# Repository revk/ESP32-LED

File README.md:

# ESP32-LED

Now at [Codeberg](https://codeberg.org/RevK/ESP32-LED)

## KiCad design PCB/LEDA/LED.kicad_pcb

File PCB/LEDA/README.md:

# LEDA

## Trademark

This is an open source project, but bear in mind you cannot sell boards or cases bearing the Andrews & Arnold Ltd name, the A&A logo, the registered trademark AJK logo, or the GS1 allocated EANs assigned to Andrews & Arnold Ltd.

## PCB Designs

These files are for use with [KiCAD](https://www.kicad.org).

- [LED](LED.kicad_pro)

## 3D

3D case designs are normally automatically created from the PCB so as to ensure correct details and placement of apertures, etc.

|Design|Bottom|Top|Combined|
|------|------|---|--------|
|LED||||

## PCB Images

---

*Auto generated README.md 2025-11-15T10:07:33*

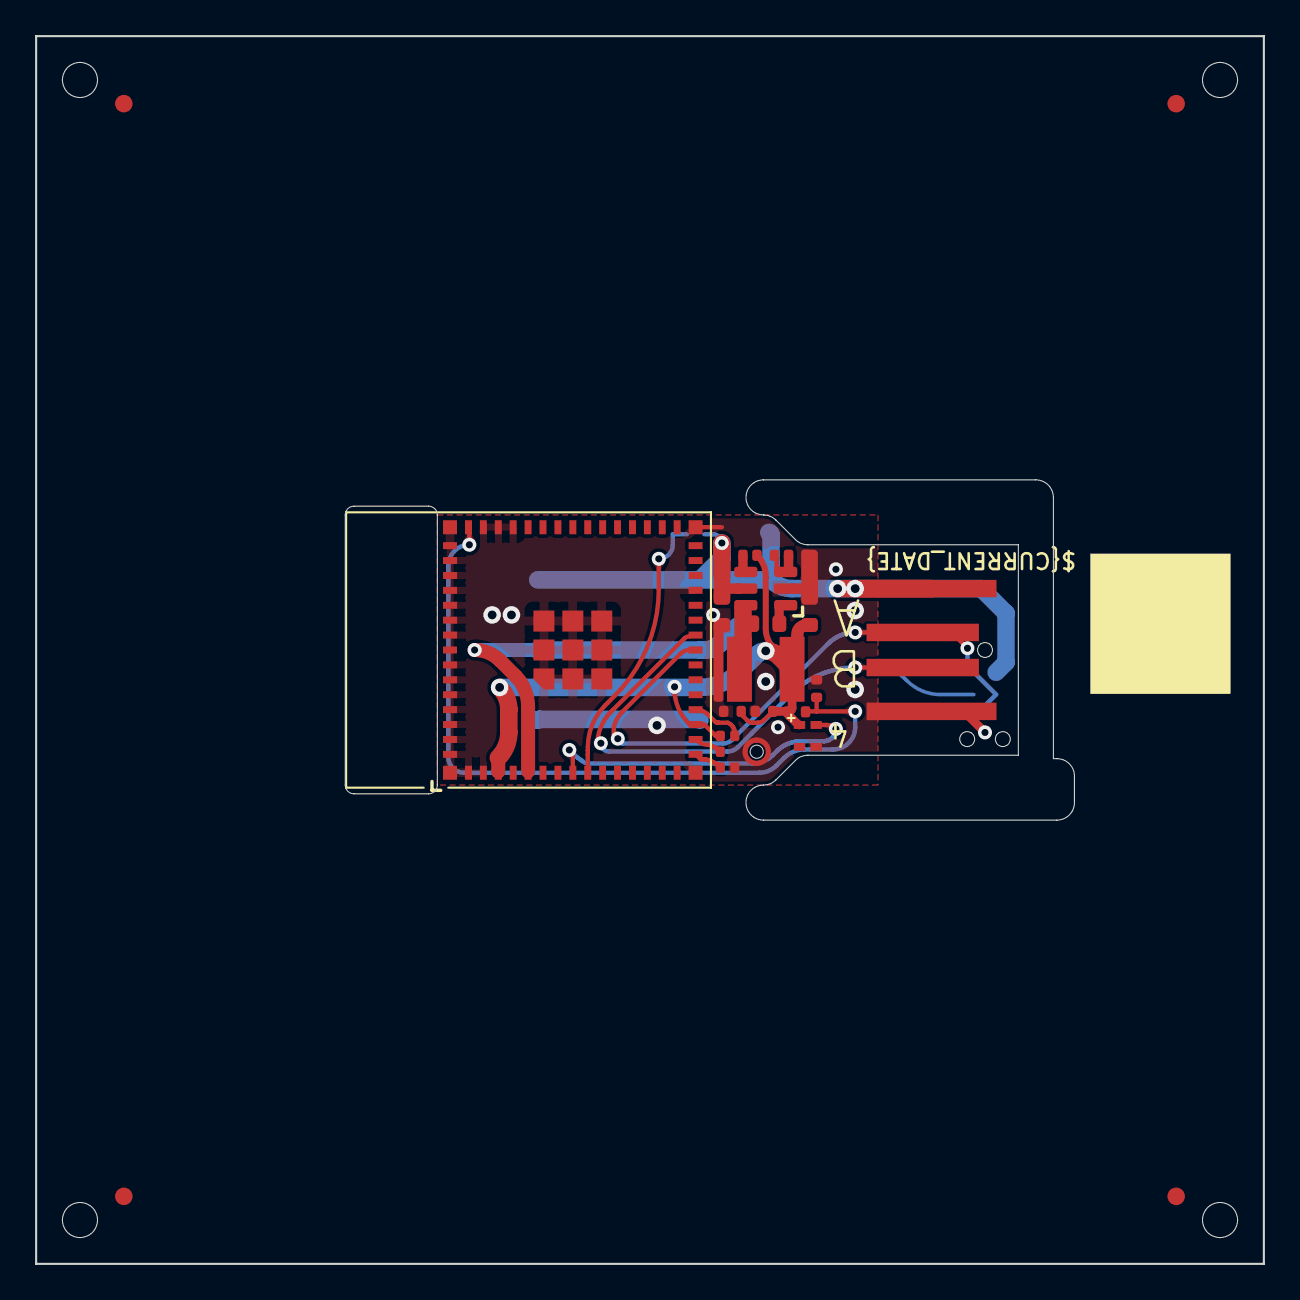
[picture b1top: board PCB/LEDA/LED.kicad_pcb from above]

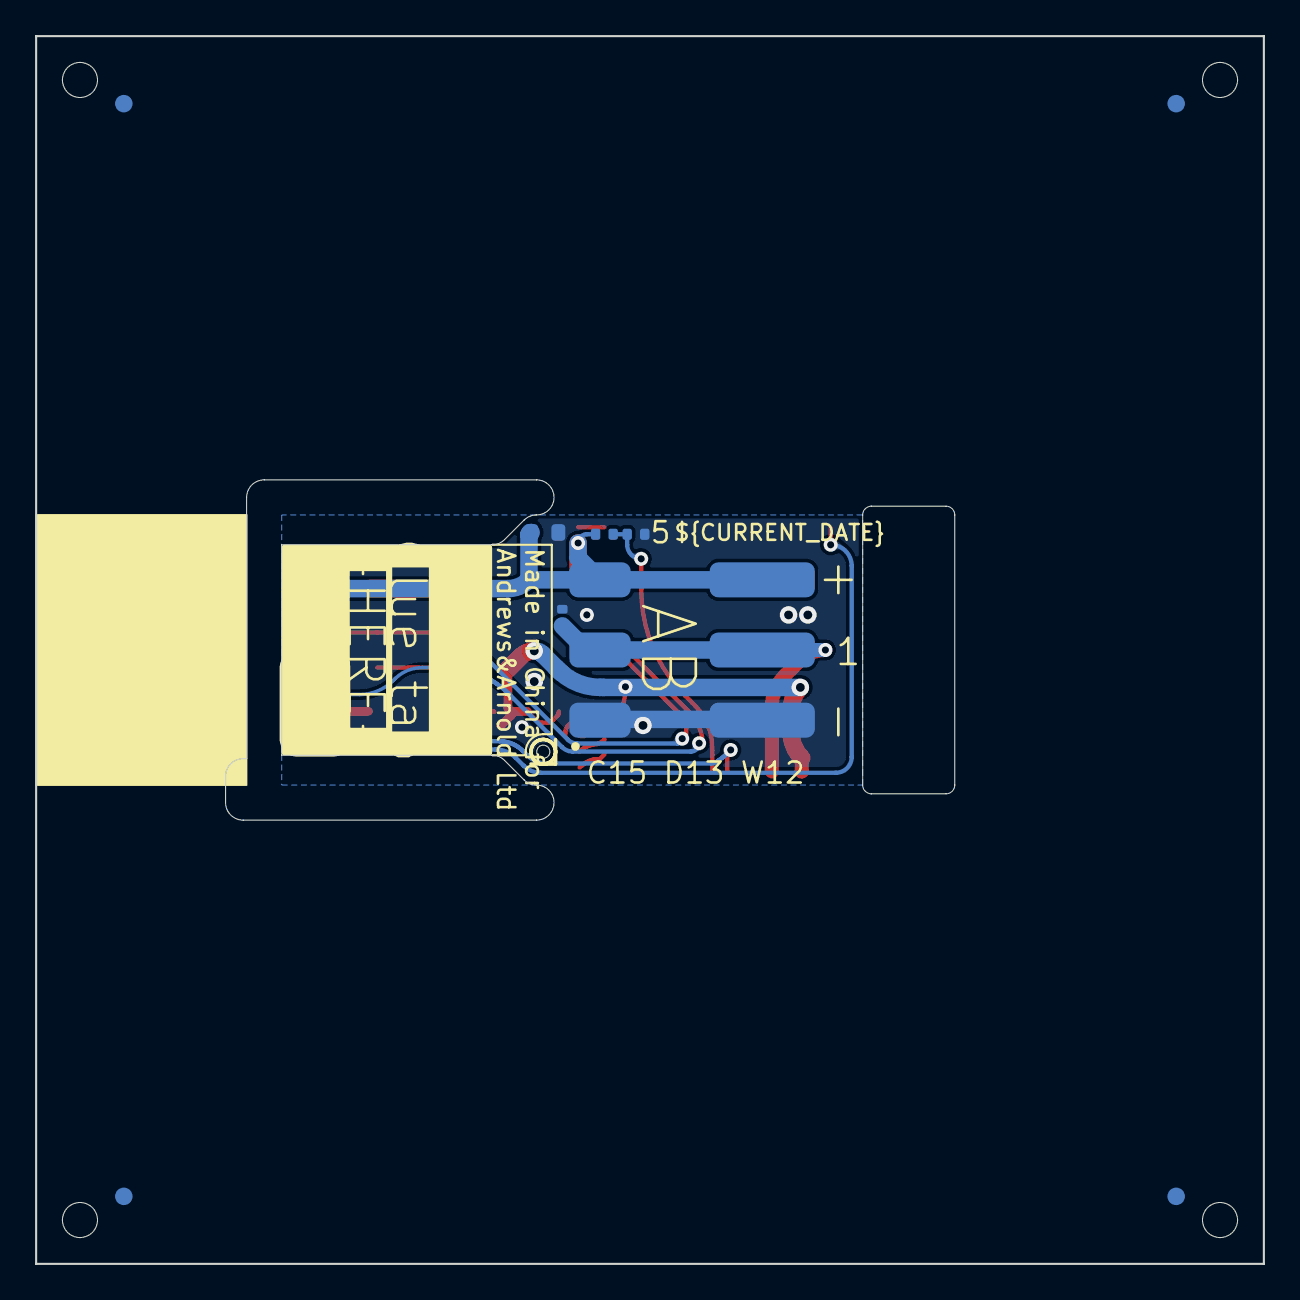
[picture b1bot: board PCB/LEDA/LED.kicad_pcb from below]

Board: 2 copper layers, 70.0 x 70.0 mm, 25 parts (8 on the bottom side), 12 nets.

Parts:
C1: 100nF; C_0402
C2: 22uF; C_0402
C3: 1uF; C_0402
C4: 10uF 35V; C_0603
C6: 10uF 35V; C_0603_
C7: 10uF 6.3V; C_0603_
C8: 100nF; C_0603_
D1: XL-1010RGBC-WS2812B; SMD1615
D2: DFN1006-2L
J1: USB_A; USB-A-PCB
J2: Conn_01x03; WAGO-2060-453-998-404-O
J3: TC2030-USB-NL-DS; Tag-Connect_TC2030-IDC-NL_2x03_P1.27mm_Vertical
L2: 10uH; L_4x4_
PCB1: 70x70; PCB7070
R1, R3: 10K; R_0402
R2: 124K; R_0402
R9: 124k; R_0402_
R10: 39k2; R_0402_
R11: 1M; R_0402_
U1: ICS43434_MEMS_Mic
U2: ESP32-S3-MINI-1
U5: MD8942; SOT-23-6-MD8942
V1, V2: 70; VCUT70N

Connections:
+3.3V: C1.1, C2.1, D1.3 (+), R1.1, U1.5 (VDD), U2.3 (3V3), U2.18 (GPIO14), U5.8 (VOUT)
ADC: R2.2, R3.1, U2.9 (GPIO5)
D+: J1.3 (D+), J3.4 (D+), U2.24 (GPIO20)
D-: J1.2 (D-), J3.2 (NC), J3.3 (D-), J3.6 (NC), U2.23 (GPIO19)
DC: C4.1, J1.1 (VBUS), J2.3, J3.1 (VBUS), R2.1, U5.5 (VIN)
GND: C1.2, C2.2, C3.2, C4.2, D1.1 (-), D2.1, J1.4 (GND), J2.1, J3.5 (GND), R3.2, U1.2 (LR), U1.3 (GND), U2.1 (GND), U2.2 (GND), U2.27 (GPIO47), U2.42 (GND), U2.43 (GND), U2.44 (GPIO46), U2.46 (GND), U2.47 (GND), U2.48 (GND), U2.49 (GND), U2.50 (GND), U2.51 (GND), U2.52 (GND), U2.53 (GND), U2.54 (GND), U2.55 (GND), U2.56 (GND), U2.57 (GND), U2.58 (GND), U2.59 (GND), U2.60 (GND), U2.61 (GND), U2.62 (GND), U2.63 (GND), U2.64 (GND), U2.65 (GND), U5.2 (GND), U5.7 (GND)
LED1: D1.2 (I), U2.8 (GPIO4)
LED2: D2.2, J2.2, U2.5 (GPIO1)
unnamed: C3.1, R1.2, U2.45 (EN)
SCK: U1.4 (SCK), U2.19 (GPIO15)
SD: U1.6 (SD), U2.17 (GPIO13)
WS: U1.1 (WS), U2.16 (GPIO12)

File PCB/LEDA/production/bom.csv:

Designator,Footprint,Quantity,Value,LCSC Part #
C1,C_0402,1,100nF,
C2,C_0402,1,22uF,
C3,C_0402,1,1uF,
C4,C_0603,1,10uF 35V,C194427
C6,C_0603_,1,10uF 35V,C194427
C7,C_0603_,1,10uF 6.3V,C1691
C8,C_0603_,1,100nF,
D1,SMD1615,1,XL-1010RGBC-WS2812B,C5349954
D2,DFN1006-2L,1,~,C5137770
J2,WAGO-2060-453-998-404,1,Conn_01x03,C2765056
L2,L_4x4_,1,10uH,
"R1, R3",R_0402,2,10K,
R10,R_0402_,1,39k2,
R11,R_0402_,1,1M,
R2,R_0402,1,124K,
R9,R_0402_,1,124k,
U1,ICS43434_MEMS_Mic,1,ICS43434_MEMS_Mic,C5656610
U2,ESP32-S3-MINI-1,1,ESP32-S3-MINI-1,C3013941
U5,SOT-23-6-MD8942,1,MD8942,C2684786

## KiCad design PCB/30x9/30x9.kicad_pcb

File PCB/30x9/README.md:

# 30x9

## Trademark

This is an open source project, but bear in mind you cannot sell boards or cases bearing the Andrews & Arnold Ltd name, the A&A logo, the registered trademark AJK logo, or the GS1 allocated EANs assigned to Andrews & Arnold Ltd.

## PCB Designs

These files are for use with [KiCAD](https://www.kicad.org).

- [30x9](30x9.kicad_pro)

## PCB Images

---

*Auto generated README.md 2025-11-09T11:15:14*

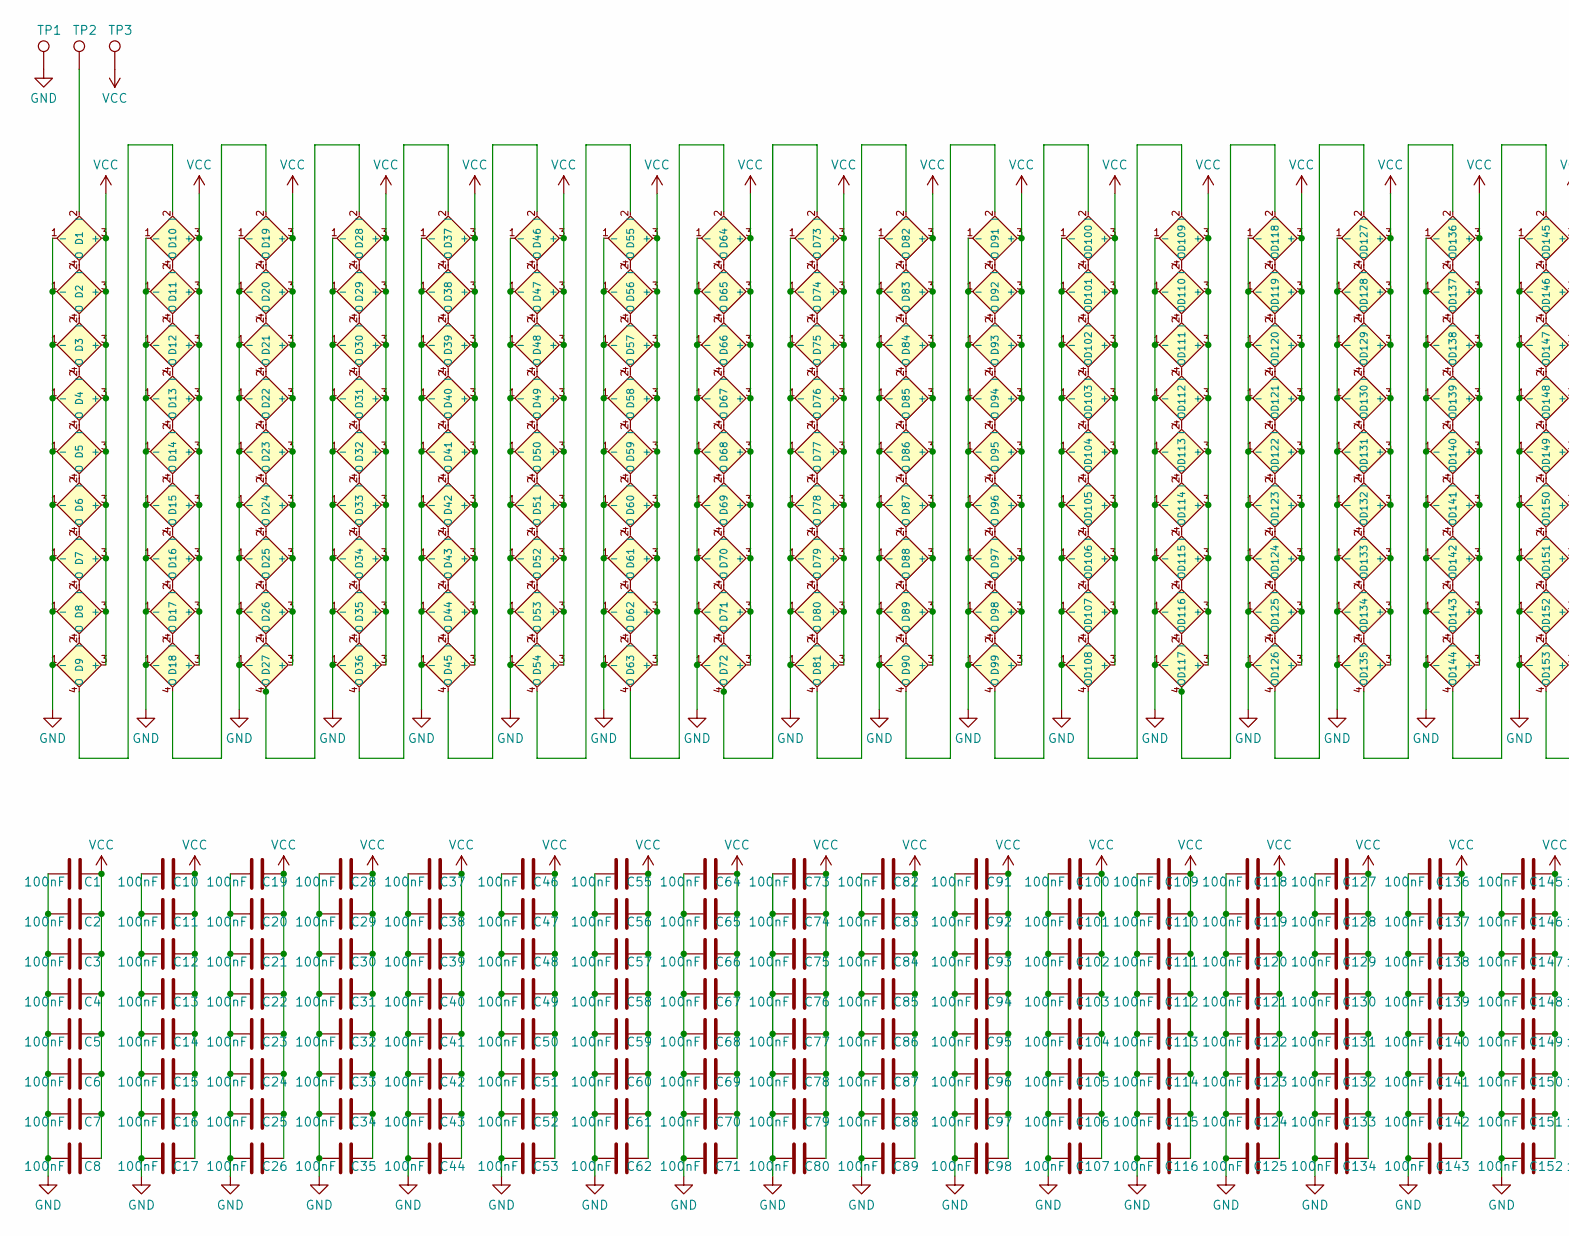
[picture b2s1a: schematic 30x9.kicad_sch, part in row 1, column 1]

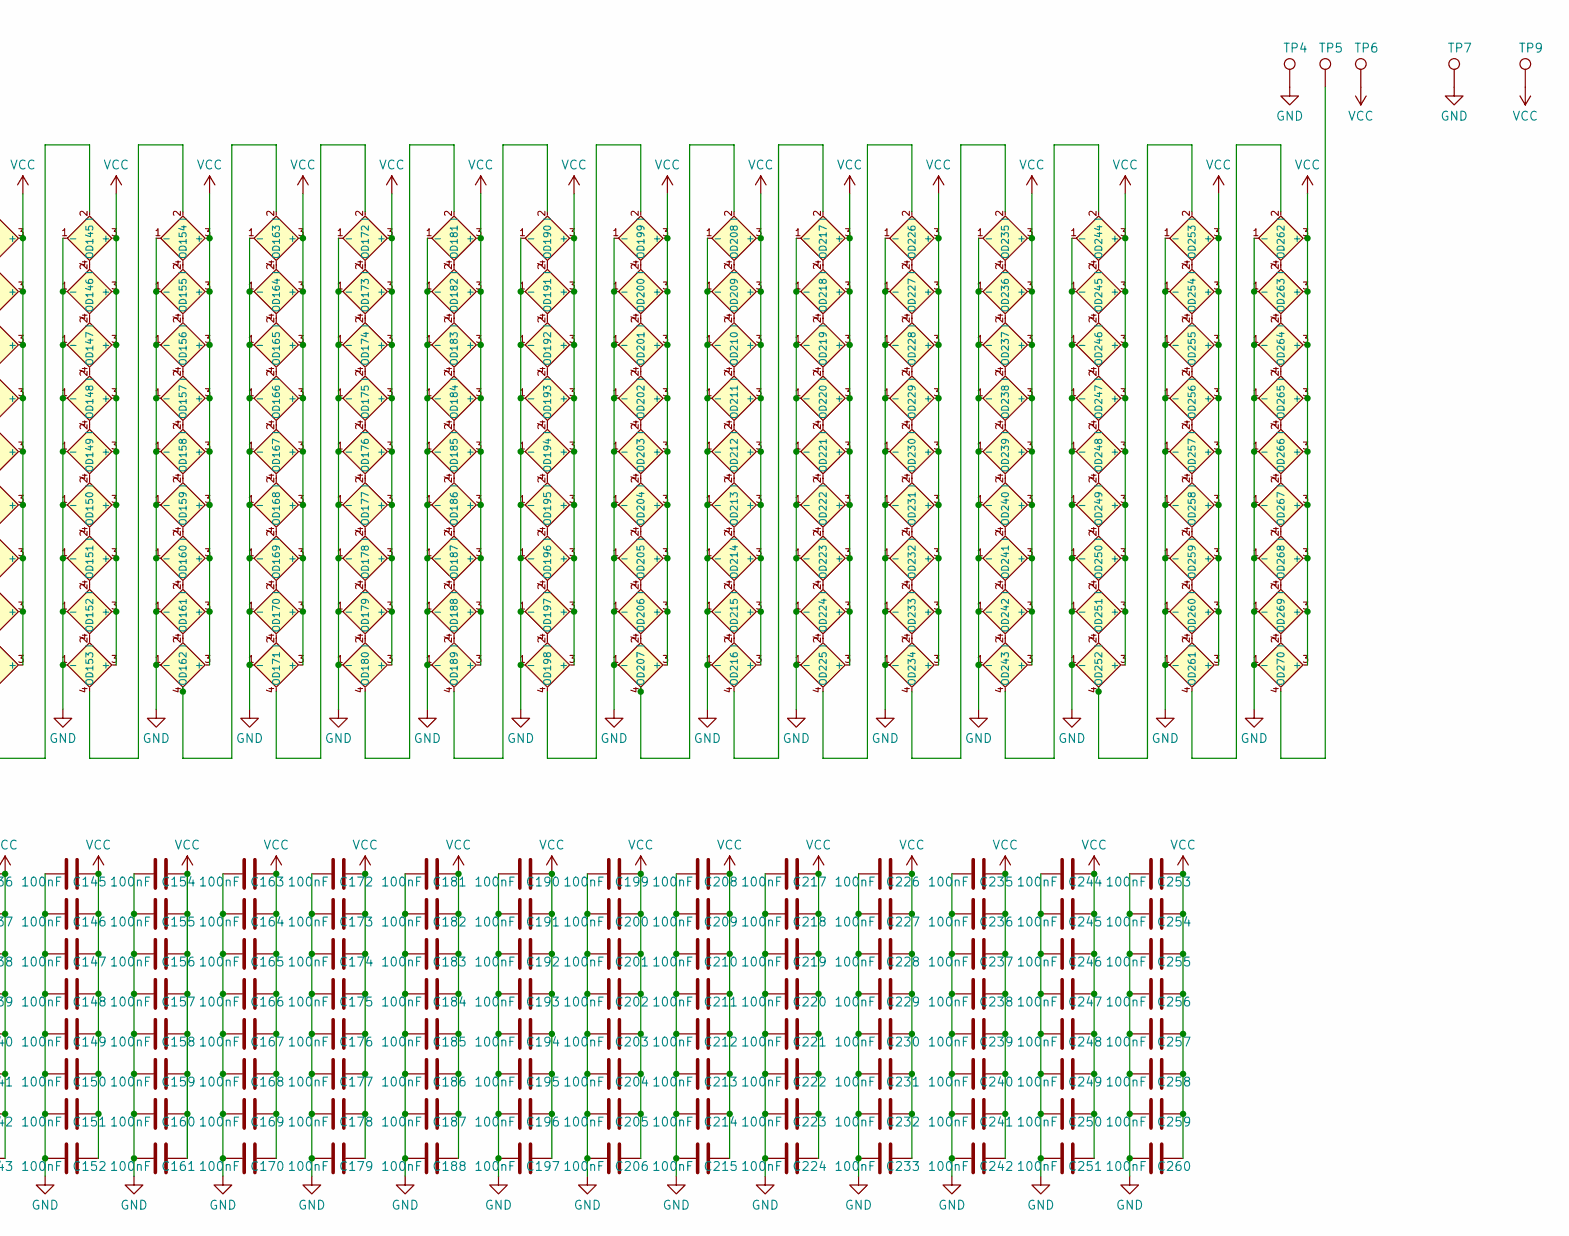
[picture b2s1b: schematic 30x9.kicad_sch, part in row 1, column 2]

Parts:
C1, C2, C3, C4, C5, C6, C7, C8, C10, C11, C12, C13, C14, C15, C16, C17, C19, C20, C21, C22, C23, C24, C25, C26, C28, C29, C30, C31, C32, C33, C34, C35, C37, C38, C39, C40, C41, C42, C43, C44, C46, C47, C48, C49, C50, C51, C52, C53, C55, C56, C57, C58, C59, C60, C61, C62, C64, C65, C66, C67, C68, C69, C70, C71, C73, C74, C75, C76, C77, C78, C79, C80, C82, C83, C84, C85, C86, C87, C88, C89, C91, C92, C93, C94, C95, C96, C97, C98, C100, C101, C102, C103, C104, C105, C106, C107, C109, C110, C111, C112, C113, C114, C115, C116, C118, C119, C120, C121, C122, C123, C124, C125, C127, C128, C129, C130, C131, C132, C133, C134, C136, C137, C138, C139, C140, C141, C142, C143, C145, C146, C147, C148, C149, C150, C151, C152, C154, C155, C156, C157, C158, C159, C160, C161, C163, C164, C165, C166, C167, C168, C169, C170, C172, C173, C174, C175, C176, C177, C178, C179, C181, C182, C183, C184, C185, C186, C187, C188, C190, C191, C192, C193, C194, C195, C196, C197, C199, C200, C201, C202, C203, C204, C205, C206, C208, C209, C210, C211, C212, C213, C214, C215, C217, C218, C219, C220, C221, C222, C223, C224, C226, C227, C228, C229, C230, C231, C232, C233, C235, C236, C237, C238, C239, C240, C241, C242, C244, C245, C246, C247, C248, C249, C250, C251, C253, C254, C255, C256, C257, C258, C259, C260: 100nF; C_0201; MPN C76934
D1, D2, D3, D4, D5, D6, D7, D8, D9, D10, D11, D12, D13, D14, D15, D16, D17, D18, D19, D20, D21, D22, D23, D24, D25, D26, D27, D28, D29, D30, D31, D32, D33, D34, D35, D36, D37, D38, D39, D40, D41, D42, D43, D44, D45, D46, D47, D48, D49, D50, D51, D52, D53, D54, D55, D56, D57, D58, D59, D60, D61, D62, D63, D64, D65, D66, D67, D68, D69, D70, D71, D72, D73, D74, D75, D76, D77, D78, D79, D80, D81, D82, D83, D84, D85, D86, D87, D88, D89, D90, D91, D92, D93, D94, D95, D96, D97, D98, D99, D100, D101, D102, D103, D104, D105, D106, D107, D108, D109, D110, D111, D112, D113, D114, D115, D116, D117, D118, D119, D120, D121, D122, D123, D124, D125, D126, D127, D128, D129, D130, D131, D132, D133, D134, D135, D136, D137, D138, D139, D140, D141, D142, D143, D144, D145, D146, D147, D148, D149, D150, D151, D152, D153, D154, D155, D156, D157, D158, D159, D160, D161, D162, D163, D164, D165, D166, D167, D168, D169, D170, D171, D172, D173, D174, D175, D176, D177, D178, D179, D180, D181, D182, D183, D184, D185, D186, D187, D188, D189, D190, D191, D192, D193, D194, D195, D196, D197, D198, D199, D200, D201, D202, D203, D204, D205, D206, D207, D208, D209, D210, D211, D212, D213, D214, D215, D216, D217, D218, D219, D220, D221, D222, D223, D224, D225, D226, D227, D228, D229, D230, D231, D232, D233, D234, D235, D236, D237, D238, D239, D240, D241, D242, D243, D244, D245, D246, D247, D248, D249, D250, D251, D252, D253, D254, D255, D256, D257, D258, D259, D260, D261, D262, D263, D264, D265, D266, D267, D268, D269, D270: XL-1010RGBC-WS2812B; SMD1615; MPN C5349954
TP1, TP2, TP3, TP4, TP5, TP6, TP7, TP9: TestPoint; PAD-2mm

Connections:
GND: C1.1, C2.1, C3.1, C4.1, C5.1, C6.1, C7.1, C8.1, C10.1, C11.1, C12.1, C13.1, C14.1, C15.1, C16.1, C17.1, C19.1, C20.1, C21.1, C22.1, C23.1, C24.1, C25.1, C26.1, C28.1, C29.1, C30.1, C31.1, C32.1, C33.1, C34.1, C35.1, C37.1, C38.1, C39.1, C40.1, C41.1, C42.1, C43.1, C44.1, C46.1, C47.1, C48.1, C49.1, C50.1, C51.1, C52.1, C53.1, C55.1, C56.1, C57.1, C58.1, C59.1, C60.1, C61.1, C62.1, C64.1, C65.1, C66.1, C67.1, C68.1, C69.1, C70.1, C71.1, C73.1, C74.1, C75.1, C76.1, C77.1, C78.1, C79.1, C80.1, C82.1, C83.1, C84.1, C85.1, C86.1, C87.1, C88.1, C89.1, C91.1, C92.1, C93.1, C94.1, C95.1, C96.1, C97.1, C98.1, C100.1, C101.1, C102.1, C103.1, C104.1, C105.1, C106.1, C107.1, C109.1, C110.1, C111.1, C112.1, C113.1, C114.1, C115.1, C116.1, C118.1, C119.1, C120.1, C121.1, C122.1, C123.1, C124.1, C125.1, C127.1, C128.1, C129.1, C130.1, C131.1, C132.1, C133.1, C134.1, C136.1, C137.1, C138.1, C139.1, C140.1, C141.1, C142.1, C143.1, C145.1, C146.1, C147.1, C148.1, C149.1, C150.1, C151.1, C152.1, C154.1, C155.1, C156.1, C157.1, C158.1, C159.1, C160.1, C161.1, C163.1, C164.1, C165.1, C166.1, C167.1, C168.1, C169.1, C170.1, C172.1, C173.1, C174.1, C175.1, C176.1, C177.1, C178.1, C179.1, C181.1, C182.1, C183.1, C184.1, C185.1, C186.1, C187.1, C188.1, C190.1, C191.1, C192.1, C193.1, C194.1, C195.1, C196.1, C197.1, C199.1, C200.1, C201.1, C202.1, C203.1, C204.1, C205.1, C206.1, C208.1, C209.1, C210.1, C211.1, C212.1, C213.1, C214.1, C215.1, C217.1, C218.1, C219.1, C220.1, C221.1, C222.1, C223.1, C224.1, C226.1, C227.1, C228.1, C229.1, C230.1, C231.1, C232.1, C233.1, C235.1, C236.1, C237.1, C238.1, C239.1, C240.1, C241.1, C242.1, C244.1, C245.1, C246.1, C247.1, C248.1, C249.1, C250.1, C251.1, C253.1, C254.1, C255.1, C256.1, C257.1, C258.1, C259.1, C260.1, D1.1 (-), D2.1 (-), D3.1 (-), D4.1 (-), D5.1 (-), D6.1 (-), D7.1 (-), D8.1 (-), D9.1 (-), D10.1 (-), D11.1 (-), D12.1 (-), D13.1 (-), D14.1 (-), D15.1 (-), D16.1 (-), D17.1 (-), D18.1 (-), D19.1 (-), D20.1 (-), D21.1 (-), D22.1 (-), D23.1 (-), D24.1 (-), D25.1 (-), D26.1 (-), D27.1 (-), D28.1 (-), D29.1 (-), D30.1 (-), D31.1 (-), D32.1 (-), D33.1 (-), D34.1 (-), D35.1 (-), D36.1 (-), D37.1 (-), D38.1 (-), D39.1 (-), D40.1 (-), D41.1 (-), D42.1 (-), D43.1 (-), D44.1 (-), D45.1 (-), D46.1 (-), D47.1 (-), D48.1 (-), D49.1 (-), D50.1 (-), D51.1 (-), D52.1 (-), D53.1 (-), D54.1 (-), D55.1 (-), D56.1 (-), D57.1 (-), D58.1 (-), D59.1 (-), D60.1 (-), D61.1 (-), D62.1 (-), D63.1 (-), D64.1 (-), D65.1 (-), D66.1 (-), D67.1 (-), D68.1 (-), D69.1 (-), D70.1 (-), D71.1 (-), D72.1 (-), D73.1 (-), D74.1 (-), D75.1 (-), D76.1 (-), D77.1 (-), D78.1 (-), D79.1 (-), D80.1 (-), D81.1 (-), D82.1 (-), D83.1 (-), D84.1 (-), D85.1 (-), D86.1 (-), D87.1 (-), D88.1 (-), D89.1 (-), D90.1 (-), D91.1 (-), D92.1 (-), D93.1 (-), D94.1 (-), D95.1 (-), D96.1 (-), D97.1 (-), D98.1 (-), D99.1 (-), D100.1 (-), D101.1 (-), D102.1 (-), D103.1 (-), D104.1 (-), D105.1 (-), D106.1 (-), D107.1 (-), D108.1 (-), D109.1 (-), D110.1 (-), D111.1 (-), D112.1 (-), D113.1 (-), D114.1 (-), D115.1 (-), D116.1 (-), D117.1 (-), D118.1 (-), D119.1 (-), D120.1 (-), D121.1 (-), D122.1 (-), D123.1 (-), D124.1 (-), D125.1 (-), D126.1 (-), D127.1 (-), D128.1 (-), D129.1 (-), D130.1 (-), D131.1 (-), D132.1 (-), D133.1 (-), D134.1 (-), D135.1 (-), D136.1 (-), D137.1 (-), D138.1 (-), D139.1 (-), D140.1 (-), D141.1 (-), D142.1 (-), D143.1 (-), D144.1 (-), D145.1 (-), D146.1 (-), D147.1 (-), D148.1 (-), D149.1 (-), D150.1 (-), D151.1 (-), D152.1 (-), D153.1 (-), D154.1 (-), D155.1 (-), D156.1 (-), D157.1 (-), D158.1 (-), D159.1 (-), D160.1 (-), D161.1 (-), D162.1 (-), D163.1 (-), D164.1 (-), D165.1 (-), D166.1 (-), D167.1 (-), D168.1 (-), D169.1 (-), D170.1 (-), D171.1 (-), D172.1 (-), D173.1 (-), D174.1 (-), D175.1 (-), D176.1 (-), D177.1 (-), D178.1 (-), D179.1 (-), D180.1 (-), D181.1 (-), D182.1 (-), D183.1 (-), D184.1 (-), D185.1 (-), D186.1 (-), D187.1 (-), D188.1 (-), D189.1 (-), D190.1 (-), D191.1 (-), D192.1 (-), D193.1 (-), D194.1 (-), D195.1 (-), D196.1 (-), D197.1 (-), D198.1 (-), D199.1 (-), D200.1 (-), D201.1 (-), D202.1 (-), D203.1 (-), D204.1 (-), D205.1 (-), D206.1 (-), D207.1 (-), D208.1 (-), D209.1 (-), D210.1 (-), D211.1 (-), D212.1 (-), D213.1 (-), D214.1 (-), D215.1 (-), D216.1 (-), D217.1 (-), D218.1 (-), D219.1 (-), D220.1 (-), D221.1 (-), D222.1 (-), D223.1 (-), D224.1 (-), D225.1 (-), D226.1 (-), D227.1 (-), D228.1 (-), D229.1 (-), D230.1 (-), D231.1 (-), D232.1 (-), D233.1 (-), D234.1 (-), D235.1 (-), D236.1 (-), D237.1 (-), D238.1 (-), D239.1 (-), D240.1 (-), D241.1 (-), D242.1 (-), D243.1 (-), D244.1 (-), D245.1 (-), D246.1 (-), D247.1 (-), D248.1 (-), D249.1 (-), D250.1 (-), D251.1 (-), D252.1 (-), D253.1 (-), D254.1 (-), D255.1 (-), D256.1 (-), D257.1 (-), D258.1 (-), D259.1 (-), D260.1 (-), D261.1 (-), D262.1 (-), D263.1 (-), D264.1 (-), D265.1 (-), D266.1 (-), D267.1 (-), D268.1 (-), D269.1 (-), D270.1 (-), TP1.1, TP4.1, TP7.1
unnamed: D1.2 (I), TP2.1
unnamed: D1.4 (O), D2.2 (I)
unnamed: D2.4 (O), D3.2 (I)
unnamed: D3.4 (O), D4.2 (I)
unnamed: D4.4 (O), D5.2 (I)
unnamed: D5.4 (O), D6.2 (I)
unnamed: D6.4 (O), D7.2 (I)
unnamed: D7.4 (O), D8.2 (I)
unnamed: D8.4 (O), D9.2 (I)
unnamed: D9.4 (O), D10.2 (I)
unnamed: D10.4 (O), D11.2 (I)
unnamed: D11.4 (O), D12.2 (I)
unnamed: D12.4 (O), D13.2 (I)
unnamed: D13.4 (O), D14.2 (I)
unnamed: D14.4 (O), D15.2 (I)
unnamed: D15.4 (O), D16.2 (I)
unnamed: D16.4 (O), D17.2 (I)
unnamed: D17.4 (O), D18.2 (I)
unnamed: D18.4 (O), D19.2 (I)
unnamed: D19.4 (O), D20.2 (I)
unnamed: D20.4 (O), D21.2 (I)
unnamed: D21.4 (O), D22.2 (I)
unnamed: D22.4 (O), D23.2 (I)
unnamed: D23.4 (O), D24.2 (I)
unnamed: D24.4 (O), D25.2 (I)
unnamed: D25.4 (O), D26.2 (I)
unnamed: D26.4 (O), D27.2 (I)
unnamed: D27.4 (O), D28.2 (I)
unnamed: D28.4 (O), D29.2 (I)
unnamed: D29.4 (O), D30.2 (I)
unnamed: D30.4 (O), D31.2 (I)
unnamed: D31.4 (O), D32.2 (I)
unnamed: D32.4 (O), D33.2 (I)
unnamed: D33.4 (O), D34.2 (I)
unnamed: D34.4 (O), D35.2 (I)
unnamed: D35.4 (O), D36.2 (I)
unnamed: D36.4 (O), D37.2 (I)
unnamed: D37.4 (O), D38.2 (I)
unnamed: D38.4 (O), D39.2 (I)
unnamed: D39.4 (O), D40.2 (I)
unnamed: D40.4 (O), D41.2 (I)
unnamed: D41.4 (O), D42.2 (I)
unnamed: D42.4 (O), D43.2 (I)
unnamed: D43.4 (O), D44.2 (I)
unnamed: D44.4 (O), D45.2 (I)
unnamed: D45.4 (O), D46.2 (I)
unnamed: D46.4 (O), D47.2 (I)
unnamed: D47.4 (O), D48.2 (I)
unnamed: D48.4 (O), D49.2 (I)
unnamed: D49.4 (O), D50.2 (I)
unnamed: D50.4 (O), D51.2 (I)
unnamed: D51.4 (O), D52.2 (I)
unnamed: D52.4 (O), D53.2 (I)
unnamed: D53.4 (O), D54.2 (I)
unnamed: D54.4 (O), D55.2 (I)
unnamed: D55.4 (O), D56.2 (I)
unnamed: D56.4 (O), D57.2 (I)
unnamed: D57.4 (O), D58.2 (I)
unnamed: D58.4 (O), D59.2 (I)
unnamed: D59.4 (O), D60.2 (I)
unnamed: D60.4 (O), D61.2 (I)
unnamed: D61.4 (O), D62.2 (I)
unnamed: D62.4 (O), D63.2 (I)
unnamed: D63.4 (O), D64.2 (I)
unnamed: D64.4 (O), D65.2 (I)
unnamed: D65.4 (O), D66.2 (I)
unnamed: D66.4 (O), D67.2 (I)
unnamed: D67.4 (O), D68.2 (I)
unnamed: D68.4 (O), D69.2 (I)
unnamed: D69.4 (O), D70.2 (I)
unnamed: D70.4 (O), D71.2 (I)
unnamed: D71.4 (O), D72.2 (I)
unnamed: D72.4 (O), D73.2 (I)
unnamed: D73.4 (O), D74.2 (I)
unnamed: D74.4 (O), D75.2 (I)
unnamed: D75.4 (O), D76.2 (I)
unnamed: D76.4 (O), D77.2 (I)
unnamed: D77.4 (O), D78.2 (I)
unnamed: D78.4 (O), D79.2 (I)
unnamed: D79.4 (O), D80.2 (I)
unnamed: D80.4 (O), D81.2 (I)
unnamed: D81.4 (O), D82.2 (I)
unnamed: D82.4 (O), D83.2 (I)
unnamed: D83.4 (O), D84.2 (I)
unnamed: D84.4 (O), D85.2 (I)
unnamed: D85.4 (O), D86.2 (I)
unnamed: D86.4 (O), D87.2 (I)
unnamed: D87.4 (O), D88.2 (I)
unnamed: D88.4 (O), D89.2 (I)
unnamed: D89.4 (O), D90.2 (I)
unnamed: D90.4 (O), D91.2 (I)
unnamed: D91.4 (O), D92.2 (I)
unnamed: D92.4 (O), D93.2 (I)
unnamed: D93.4 (O), D94.2 (I)
unnamed: D94.4 (O), D95.2 (I)
unnamed: D95.4 (O), D96.2 (I)
unnamed: D96.4 (O), D97.2 (I)
unnamed: D97.4 (O), D98.2 (I)
unnamed: D98.4 (O), D99.2 (I)
unnamed: D99.4 (O), D100.2 (I)
unnamed: D100.4 (O), D101.2 (I)
unnamed: D101.4 (O), D102.2 (I)
unnamed: D102.4 (O), D103.2 (I)
unnamed: D103.4 (O), D104.2 (I)
unnamed: D104.4 (O), D105.2 (I)
unnamed: D105.4 (O), D106.2 (I)
unnamed: D106.4 (O), D107.2 (I)
unnamed: D107.4 (O), D108.2 (I)
unnamed: D108.4 (O), D109.2 (I)
unnamed: D109.4 (O), D110.2 (I)
unnamed: D110.4 (O), D111.2 (I)
unnamed: D111.4 (O), D112.2 (I)
unnamed: D112.4 (O), D113.2 (I)
unnamed: D113.4 (O), D114.2 (I)
unnamed: D114.4 (O), D115.2 (I)
unnamed: D115.4 (O), D116.2 (I)
unnamed: D116.4 (O), D117.2 (I)
unnamed: D117.4 (O), D118.2 (I)
unnamed: D118.4 (O), D119.2 (I)
unnamed: D119.4 (O), D120.2 (I)
unnamed: D120.4 (O), D121.2 (I)
unnamed: D121.4 (O), D122.2 (I)
unnamed: D122.4 (O), D123.2 (I)
unnamed: D123.4 (O), D124.2 (I)
unnamed: D124.4 (O), D125.2 (I)
unnamed: D125.4 (O), D126.2 (I)
unnamed: D126.4 (O), D127.2 (I)
unnamed: D127.4 (O), D128.2 (I)
unnamed: D128.4 (O), D129.2 (I)
unnamed: D129.4 (O), D130.2 (I)
unnamed: D130.4 (O), D131.2 (I)
unnamed: D131.4 (O), D132.2 (I)
unnamed: D132.4 (O), D133.2 (I)
unnamed: D133.4 (O), D134.2 (I)
unnamed: D134.4 (O), D135.2 (I)
unnamed: D135.4 (O), D136.2 (I)
unnamed: D136.4 (O), D137.2 (I)
unnamed: D137.4 (O), D138.2 (I)
unnamed: D138.4 (O), D139.2 (I)
unnamed: D139.4 (O), D140.2 (I)
unnamed: D140.4 (O), D141.2 (I)
unnamed: D141.4 (O), D142.2 (I)
unnamed: D142.4 (O), D143.2 (I)
unnamed: D143.4 (O), D144.2 (I)
unnamed: D144.4 (O), D145.2 (I)
unnamed: D145.4 (O), D146.2 (I)
unnamed: D146.4 (O), D147.2 (I)
unnamed: D147.4 (O), D148.2 (I)
unnamed: D148.4 (O), D149.2 (I)
unnamed: D149.4 (O), D150.2 (I)
unnamed: D150.4 (O), D151.2 (I)
unnamed: D151.4 (O), D152.2 (I)
unnamed: D152.4 (O), D153.2 (I)
unnamed: D153.4 (O), D154.2 (I)
unnamed: D154.4 (O), D155.2 (I)
unnamed: D155.4 (O), D156.2 (I)
unnamed: D156.4 (O), D157.2 (I)
unnamed: D157.4 (O), D158.2 (I)
unnamed: D158.4 (O), D159.2 (I)
unnamed: D159.4 (O), D160.2 (I)
unnamed: D160.4 (O), D161.2 (I)
unnamed: D161.4 (O), D162.2 (I)
unnamed: D162.4 (O), D163.2 (I)
unnamed: D163.4 (O), D164.2 (I)
unnamed: D164.4 (O), D165.2 (I)
unnamed: D165.4 (O), D166.2 (I)
unnamed: D166.4 (O), D167.2 (I)
unnamed: D167.4 (O), D168.2 (I)
unnamed: D168.4 (O), D169.2 (I)
unnamed: D169.4 (O), D170.2 (I)
unnamed: D170.4 (O), D171.2 (I)
unnamed: D171.4 (O), D172.2 (I)
unnamed: D172.4 (O), D173.2 (I)
unnamed: D173.4 (O), D174.2 (I)
unnamed: D174.4 (O), D175.2 (I)
unnamed: D175.4 (O), D176.2 (I)
unnamed: D176.4 (O), D177.2 (I)
unnamed: D177.4 (O), D178.2 (I)
unnamed: D178.4 (O), D179.2 (I)
unnamed: D179.4 (O), D180.2 (I)
unnamed: D180.4 (O), D181.2 (I)
unnamed: D181.4 (O), D182.2 (I)
unnamed: D182.4 (O), D183.2 (I)
unnamed: D183.4 (O), D184.2 (I)
unnamed: D184.4 (O), D185.2 (I)
unnamed: D185.4 (O), D186.2 (I)
unnamed: D186.4 (O), D187.2 (I)
unnamed: D187.4 (O), D188.2 (I)
unnamed: D188.4 (O), D189.2 (I)
unnamed: D189.4 (O), D190.2 (I)
unnamed: D190.4 (O), D191.2 (I)
unnamed: D191.4 (O), D192.2 (I)
unnamed: D192.4 (O), D193.2 (I)
unnamed: D193.4 (O), D194.2 (I)
unnamed: D194.4 (O), D195.2 (I)
unnamed: D195.4 (O), D196.2 (I)
unnamed: D196.4 (O), D197.2 (I)
unnamed: D197.4 (O), D198.2 (I)
unnamed: D198.4 (O), D199.2 (I)
unnamed: D199.4 (O), D200.2 (I)
unnamed: D200.4 (O), D201.2 (I)
unnamed: D201.4 (O), D202.2 (I)
unnamed: D202.4 (O), D203.2 (I)
unnamed: D203.4 (O), D204.2 (I)
unnamed: D204.4 (O), D205.2 (I)
unnamed: D205.4 (O), D206.2 (I)
unnamed: D206.4 (O), D207.2 (I)
unnamed: D207.4 (O), D208.2 (I)
unnamed: D208.4 (O), D209.2 (I)
unnamed: D209.4 (O), D210.2 (I)
unnamed: D210.4 (O), D211.2 (I)
unnamed: D211.4 (O), D212.2 (I)
unnamed: D212.4 (O), D213.2 (I)
unnamed: D213.4 (O), D214.2 (I)
unnamed: D214.4 (O), D215.2 (I)
unnamed: D215.4 (O), D216.2 (I)
unnamed: D216.4 (O), D217.2 (I)
unnamed: D217.4 (O), D218.2 (I)
unnamed: D218.4 (O), D219.2 (I)
unnamed: D219.4 (O), D220.2 (I)
unnamed: D220.4 (O), D221.2 (I)
unnamed: D221.4 (O), D222.2 (I)
unnamed: D222.4 (O), D223.2 (I)
unnamed: D223.4 (O), D224.2 (I)
unnamed: D224.4 (O), D225.2 (I)
unnamed: D225.4 (O), D226.2 (I)
unnamed: D226.4 (O), D227.2 (I)
unnamed: D227.4 (O), D228.2 (I)
unnamed: D228.4 (O), D229.2 (I)
unnamed: D229.4 (O), D230.2 (I)
unnamed: D230.4 (O), D231.2 (I)
unnamed: D231.4 (O), D232.2 (I)
unnamed: D232.4 (O), D233.2 (I)
unnamed: D233.4 (O), D234.2 (I)
unnamed: D234.4 (O), D235.2 (I)
unnamed: D235.4 (O), D236.2 (I)
unnamed: D236.4 (O), D237.2 (I)
unnamed: D237.4 (O), D238.2 (I)
unnamed: D238.4 (O), D239.2 (I)
unnamed: D239.4 (O), D240.2 (I)
unnamed: D240.4 (O), D241.2 (I)
unnamed: D241.4 (O), D242.2 (I)
unnamed: D242.4 (O), D243.2 (I)
unnamed: D243.4 (O), D244.2 (I)
unnamed: D244.4 (O), D245.2 (I)
unnamed: D245.4 (O), D246.2 (I)
unnamed: D246.4 (O), D247.2 (I)
unnamed: D247.4 (O), D248.2 (I)
unnamed: D248.4 (O), D249.2 (I)
unnamed: D249.4 (O), D250.2 (I)
unnamed: D250.4 (O), D251.2 (I)
unnamed: D251.4 (O), D252.2 (I)
unnamed: D252.4 (O), D253.2 (I)
unnamed: D253.4 (O), D254.2 (I)
unnamed: D254.4 (O), D255.2 (I)
unnamed: D255.4 (O), D256.2 (I)
unnamed: D256.4 (O), D257.2 (I)
unnamed: D257.4 (O), D258.2 (I)
unnamed: D258.4 (O), D259.2 (I)
unnamed: D259.4 (O), D260.2 (I)
unnamed: D260.4 (O), D261.2 (I)
unnamed: D261.4 (O), D262.2 (I)
unnamed: D262.4 (O), D263.2 (I)
unnamed: D263.4 (O), D264.2 (I)
unnamed: D264.4 (O), D265.2 (I)
unnamed: D265.4 (O), D266.2 (I)
unnamed: D266.4 (O), D267.2 (I)
unnamed: D267.4 (O), D268.2 (I)
unnamed: D268.4 (O), D269.2 (I)
unnamed: D269.4 (O), D270.2 (I)
unnamed: D270.4 (O), TP5.1
VCC: C1.2, C2.2, C3.2, C4.2, C5.2, C6.2, C7.2, C8.2, C10.2, C11.2, C12.2, C13.2, C14.2, C15.2, C16.2, C17.2, C19.2, C20.2, C21.2, C22.2, C23.2, C24.2, C25.2, C26.2, C28.2, C29.2, C30.2, C31.2, C32.2, C33.2, C34.2, C35.2, C37.2, C38.2, C39.2, C40.2, C41.2, C42.2, C43.2, C44.2, C46.2, C47.2, C48.2, C49.2, C50.2, C51.2, C52.2, C53.2, C55.2, C56.2, C57.2, C58.2, C59.2, C60.2, C61.2, C62.2, C64.2, C65.2, C66.2, C67.2, C68.2, C69.2, C70.2, C71.2, C73.2, C74.2, C75.2, C76.2, C77.2, C78.2, C79.2, C80.2, C82.2, C83.2, C84.2, C85.2, C86.2, C87.2, C88.2, C89.2, C91.2, C92.2, C93.2, C94.2, C95.2, C96.2, C97.2, C98.2, C100.2, C101.2, C102.2, C103.2, C104.2, C105.2, C106.2, C107.2, C109.2, C110.2, C111.2, C112.2, C113.2, C114.2, C115.2, C116.2, C118.2, C119.2, C120.2, C121.2, C122.2, C123.2, C124.2, C125.2, C127.2, C128.2, C129.2, C130.2, C131.2, C132.2, C133.2, C134.2, C136.2, C137.2, C138.2, C139.2, C140.2, C141.2, C142.2, C143.2, C145.2, C146.2, C147.2, C148.2, C149.2, C150.2, C151.2, C152.2, C154.2, C155.2, C156.2, C157.2, C158.2, C159.2, C160.2, C161.2, C163.2, C164.2, C165.2, C166.2, C167.2, C168.2, C169.2, C170.2, C172.2, C173.2, C174.2, C175.2, C176.2, C177.2, C178.2, C179.2, C181.2, C182.2, C183.2, C184.2, C185.2, C186.2, C187.2, C188.2, C190.2, C191.2, C192.2, C193.2, C194.2, C195.2, C196.2, C197.2, C199.2, C200.2, C201.2, C202.2, C203.2, C204.2, C205.2, C206.2, C208.2, C209.2, C210.2, C211.2, C212.2, C213.2, C214.2, C215.2, C217.2, C218.2, C219.2, C220.2, C221.2, C222.2, C223.2, C224.2, C226.2, C227.2, C228.2, C229.2, C230.2, C231.2, C232.2, C233.2, C235.2, C236.2, C237.2, C238.2, C239.2, C240.2, C241.2, C242.2, C244.2, C245.2, C246.2, C247.2, C248.2, C249.2, C250.2, C251.2, C253.2, C254.2, C255.2, C256.2, C257.2, C258.2, C259.2, C260.2, D1.3 (+), D2.3 (+), D3.3 (+), D4.3 (+), D5.3 (+), D6.3 (+), D7.3 (+), D8.3 (+), D9.3 (+), D10.3 (+), D11.3 (+), D12.3 (+), D13.3 (+), D14.3 (+), D15.3 (+), D16.3 (+), D17.3 (+), D18.3 (+), D19.3 (+), D20.3 (+), D21.3 (+), D22.3 (+), D23.3 (+), D24.3 (+), D25.3 (+), D26.3 (+), D27.3 (+), D28.3 (+), D29.3 (+), D30.3 (+), D31.3 (+), D32.3 (+), D33.3 (+), D34.3 (+), D35.3 (+), D36.3 (+), D37.3 (+), D38.3 (+), D39.3 (+), D40.3 (+), D41.3 (+), D42.3 (+), D43.3 (+), D44.3 (+), D45.3 (+), D46.3 (+), D47.3 (+), D48.3 (+), D49.3 (+), D50.3 (+), D51.3 (+), D52.3 (+), D53.3 (+), D54.3 (+), D55.3 (+), D56.3 (+), D57.3 (+), D58.3 (+), D59.3 (+), D60.3 (+), D61.3 (+), D62.3 (+), D63.3 (+), D64.3 (+), D65.3 (+), D66.3 (+), D67.3 (+), D68.3 (+), D69.3 (+), D70.3 (+), D71.3 (+), D72.3 (+), D73.3 (+), D74.3 (+), D75.3 (+), D76.3 (+), D77.3 (+), D78.3 (+), D79.3 (+), D80.3 (+), D81.3 (+), D82.3 (+), D83.3 (+), D84.3 (+), D85.3 (+), D86.3 (+), D87.3 (+), D88.3 (+), D89.3 (+), D90.3 (+), D91.3 (+), D92.3 (+), D93.3 (+), D94.3 (+), D95.3 (+), D96.3 (+), D97.3 (+), D98.3 (+), D99.3 (+), D100.3 (+), D101.3 (+), D102.3 (+), D103.3 (+), D104.3 (+), D105.3 (+), D106.3 (+), D107.3 (+), D108.3 (+), D109.3 (+), D110.3 (+), D111.3 (+), D112.3 (+), D113.3 (+), D114.3 (+), D115.3 (+), D116.3 (+), D117.3 (+), D118.3 (+), D119.3 (+), D120.3 (+), D121.3 (+), D122.3 (+), D123.3 (+), D124.3 (+), D125.3 (+), D126.3 (+), D127.3 (+), D128.3 (+), D129.3 (+), D130.3 (+), D131.3 (+), D132.3 (+), D133.3 (+), D134.3 (+), D135.3 (+), D136.3 (+), D137.3 (+), D138.3 (+), D139.3 (+), D140.3 (+), D141.3 (+), D142.3 (+), D143.3 (+), D144.3 (+), D145.3 (+), D146.3 (+), D147.3 (+), D148.3 (+), D149.3 (+), D150.3 (+), D151.3 (+), D152.3 (+), D153.3 (+), D154.3 (+), D155.3 (+), D156.3 (+), D157.3 (+), D158.3 (+), D159.3 (+), D160.3 (+), D161.3 (+), D162.3 (+), D163.3 (+), D164.3 (+), D165.3 (+), D166.3 (+), D167.3 (+), D168.3 (+), D169.3 (+), D170.3 (+), D171.3 (+), D172.3 (+), D173.3 (+), D174.3 (+), D175.3 (+), D176.3 (+), D177.3 (+), D178.3 (+), D179.3 (+), D180.3 (+), D181.3 (+), D182.3 (+), D183.3 (+), D184.3 (+), D185.3 (+), D186.3 (+), D187.3 (+), D188.3 (+), D189.3 (+), D190.3 (+), D191.3 (+), D192.3 (+), D193.3 (+), D194.3 (+), D195.3 (+), D196.3 (+), D197.3 (+), D198.3 (+), D199.3 (+), D200.3 (+), D201.3 (+), D202.3 (+), D203.3 (+), D204.3 (+), D205.3 (+), D206.3 (+), D207.3 (+), D208.3 (+), D209.3 (+), D210.3 (+), D211.3 (+), D212.3 (+), D213.3 (+), D214.3 (+), D215.3 (+), D216.3 (+), D217.3 (+), D218.3 (+), D219.3 (+), D220.3 (+), D221.3 (+), D222.3 (+), D223.3 (+), D224.3 (+), D225.3 (+), D226.3 (+), D227.3 (+), D228.3 (+), D229.3 (+), D230.3 (+), D231.3 (+), D232.3 (+), D233.3 (+), D234.3 (+), D235.3 (+), D236.3 (+), D237.3 (+), D238.3 (+), D239.3 (+), D240.3 (+), D241.3 (+), D242.3 (+), D243.3 (+), D244.3 (+), D245.3 (+), D246.3 (+), D247.3 (+), D248.3 (+), D249.3 (+), D250.3 (+), D251.3 (+), D252.3 (+), D253.3 (+), D254.3 (+), D255.3 (+), D256.3 (+), D257.3 (+), D258.3 (+), D259.3 (+), D260.3 (+), D261.3 (+), D262.3 (+), D263.3 (+), D264.3 (+), D265.3 (+), D266.3 (+), D267.3 (+), D268.3 (+), D269.3 (+), D270.3 (+), TP3.1, TP6.1, TP9.1

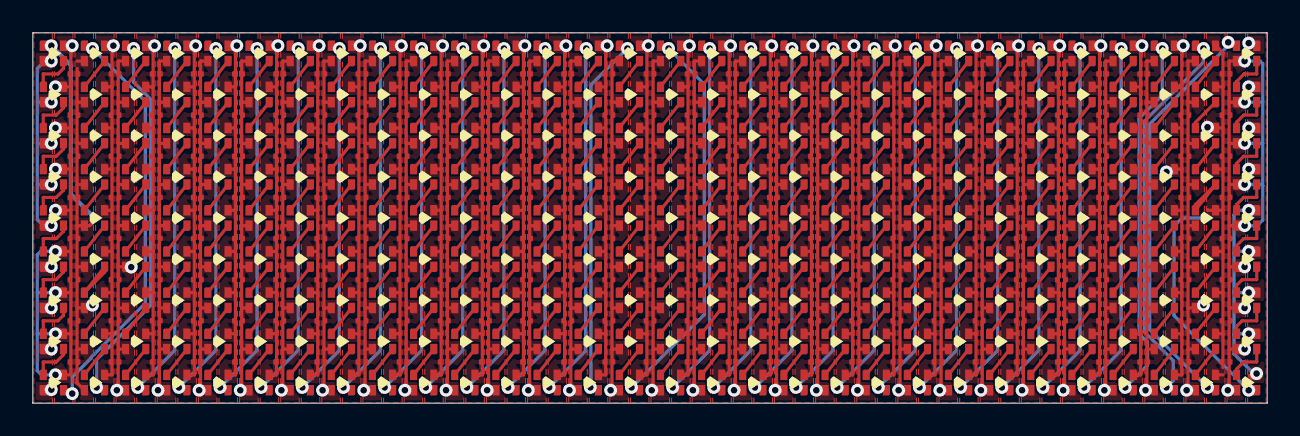
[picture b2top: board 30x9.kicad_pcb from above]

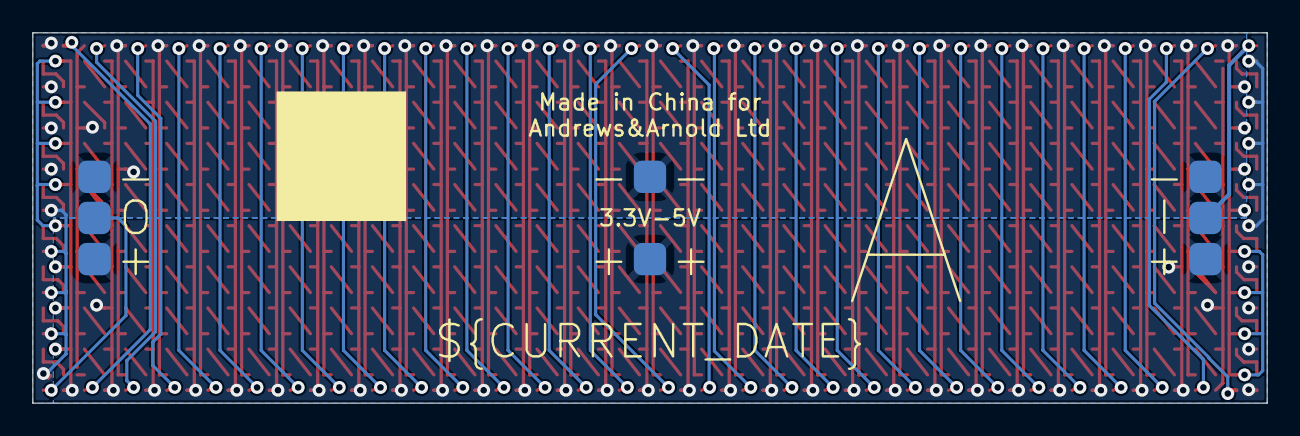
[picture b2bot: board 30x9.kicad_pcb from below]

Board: 2 copper layers, 76.2 x 22.9 mm, 510 parts (8 on the bottom side), 273 nets.

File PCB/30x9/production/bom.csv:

Designator,Footprint,Quantity,Value,LCSC Part #
"C1, C10, C100, C101, C102, C103, C104, C105, C106, C107, C109, C11, C110, C111, C112, C113, C114, C115, C116, C118, C119, C12, C120, C121, C122, C123, C124, C125, C127, C128, C129, C13, C130, C131, C132, C133, C134, C136, C137, C138, C139, C14, C140, C141, C142, C143, C145, C146, C147, C148, C149, C15, C150, C151, C152, C154, C155, C156, C157, C158, C159, C16, C160, C161, C163, C164, C165, C166, C167, C168, C169, C17, C170, C172, C173, C174, C175, C176, C177, C178, C179, C181, C182, C183, C184, C185, C186, C187, C188, C19, C190, C191, C192, C193, C194, C195, C196, C197, C199, C2, C20, C200, C201, C202, C203, C204, C205, C206, C208, C209, C21, C210, C211, C212, C213, C214, C215, C217, C218, C219, C22, C220, C221, C222, C223, C224, C226, C227, C228, C229, C23, C230, C231, C232, C233, C235, C236, C237, C238, C239, C24, C240, C241, C242, C244, C245, C246, C247, C248, C249, C25, C250, C251, C253, C254, C255, C256, C257, C258, C259, C26, C260, C28, C29, C3, C30, C31, C32, C33, C34, C35, C37, C38, C39, C4, C40, C41, C42, C43, C44, C46, C47, C48, C49, C5, C50, C51, C52, C53, C55, C56, C57, C58, C59, C6, C60, C61, C62, C64, C65",C_0201,200,100nF,C76934
"C66, C67, C68, C69, C7, C70, C71, C73, C74, C75, C76, C77, C78, C79, C8, C80, C82, C83, C84, C85, C86, C87, C88, C89, C91, C92, C93, C94, C95, C96, C97, C98",C_0201,32,100nF,C76934
"D1, D10, D100, D101, D102, D103, D104, D105, D106, D107, D108, D109, D11, D110, D111, D112, D113, D114, D115, D116, D117, D118, D119, D12, D120, D121, D122, D123, D124, D125, D126, D127, D128, D129, D13, D130, D131, D132, D133, D134, D135, D136, D137, D138, D139, D14, D140, D141, D142, D143, D144, D145, D146, D147, D148, D149, D15, D150, D151, D152, D153, D154, D155, D156, D157, D158, D159, D16, D160, D161, D162, D163, D164, D165, D166, D167, D168, D169, D17, D170, D171, D172, D173, D174, D175, D176, D177, D178, D179, D18, D180, D181, D182, D183, D184, D185, D186, D187, D188, D189, D19, D190, D191, D192, D193, D194, D195, D196, D197, D198, D199, D2, D20, D200, D201, D202, D203, D204, D205, D206, D207, D208, D209, D21, D210, D211, D212, D213, D214, D215, D216, D217, D218, D219, D22, D220, D221, D222, D223, D224, D225, D226, D227, D228, D229, D23, D230, D231, D232, D233, D234, D235, D236, D237, D238, D239, D24, D240, D241, D242, D243, D244, D245, D246, D247, D248, D249, D25, D250, D251, D252, D253, D254, D255, D256, D257, D258, D259, D26, D260, D261, D262, D263, D264, D265, D266, D267, D268, D269, D27, D270, D28, D29, D3, D30, D31, D32, D33, D34, D35",SMD1615,200,XL-1010RGBC-WS2812B,C5349954
"D36, D37, D38, D39, D4, D40, D41, D42, D43, D44, D45, D46, D47, D48, D49, D5, D50, D51, D52, D53, D54, D55, D56, D57, D58, D59, D6, D60, D61, D62, D63, D64, D65, D66, D67, D68, D69, D7, D70, D71, D72, D73, D74, D75, D76, D77, D78, D79, D8, D80, D81, D82, D83, D84, D85, D86, D87, D88, D89, D9, D90, D91, D92, D93, D94, D95, D96, D97, D98, D99",SMD1615,70,XL-1010RGBC-WS2812B,C5349954
"TP1, TP2, TP3, TP4, TP5, TP6, TP7, TP9",PAD-2mm,8,TestPoint,
